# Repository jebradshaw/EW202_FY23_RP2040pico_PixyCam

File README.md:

# EW202_FY23_RP2040pico_PixyCam

  This PCB uses a Raspberry Pie RP2040 Pico microcontroller to interface with a PixyCam5 camera through an SPI interface to track a color object
using a dual servo pan and tilt platform.  There are also two potentiometers for a manual control of the servos.  This board is used in the WRC 
department at the US Naval Academy in support of the EW202 principles of Mechatronics course.

3D Rendering in KiCad of PCB

Schematic in KiCad

KiCad PCB file

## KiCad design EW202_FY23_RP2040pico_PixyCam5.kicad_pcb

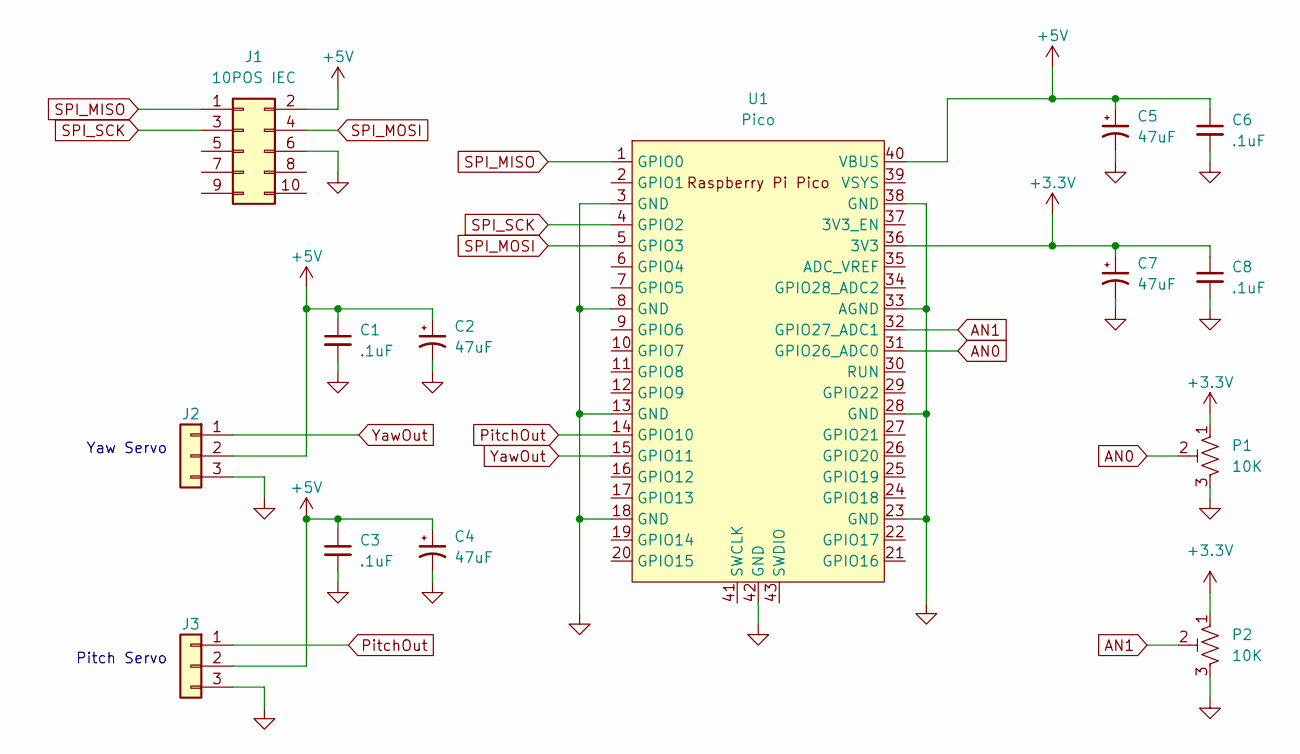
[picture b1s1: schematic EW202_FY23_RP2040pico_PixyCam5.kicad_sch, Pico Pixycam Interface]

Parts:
C1, C3, C6, C8: .1uF; C_Disc_D3.4mm_W2.1mm_P2.50mm
C2, C4, C5, C7: 47uF; CP_Radial_D5.0mm_P2.00mm
J1: 10POS IEC; IDC-Header_2x05_P2.54mm_Vertical
J2, J3: Conn_01x03; PinHeader_1x03_P2.54mm_Vertical
P1, P2: 10K; Potentiometer_Bourns_3362P-1-103TLF doublePads
U1: Pico; RPi_Pico_SMD_TH

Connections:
+3.3V: C7.1, C8.1, P1.1, P2.1, U1.36 (3V3)
+5V: C1.1, C2.1, C3.1, C4.1, C5.1, C6.1, J1.2, J2.2, J3.2, U1.40 (VBUS)
AN0: P1.2, U1.31 (GPIO26_ADC0)
AN1: P2.2, U1.32 (GPIO27_ADC1)
GND: C1.2, C2.2, C3.2, C4.2, C5.2, C6.2, C7.2, C8.2, J1.6, J2.3, J3.3, P1.3, P2.3, U1.3 (GND), U1.8 (GND), U1.13 (GND), U1.18 (GND), U1.23 (GND), U1.28 (GND), U1.33 (AGND), U1.38 (GND), U1.42 (GND)
PitchOut: J3.1, U1.14 (GPIO10)
SPI_MISO: J1.1, U1.1 (GPIO0)
SPI_MOSI: J1.4, U1.5 (GPIO3)
SPI_SCK: J1.3, U1.4 (GPIO2)
YawOut: J2.1, U1.15 (GPIO11)

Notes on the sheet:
Pitch Servo
Yaw Servo

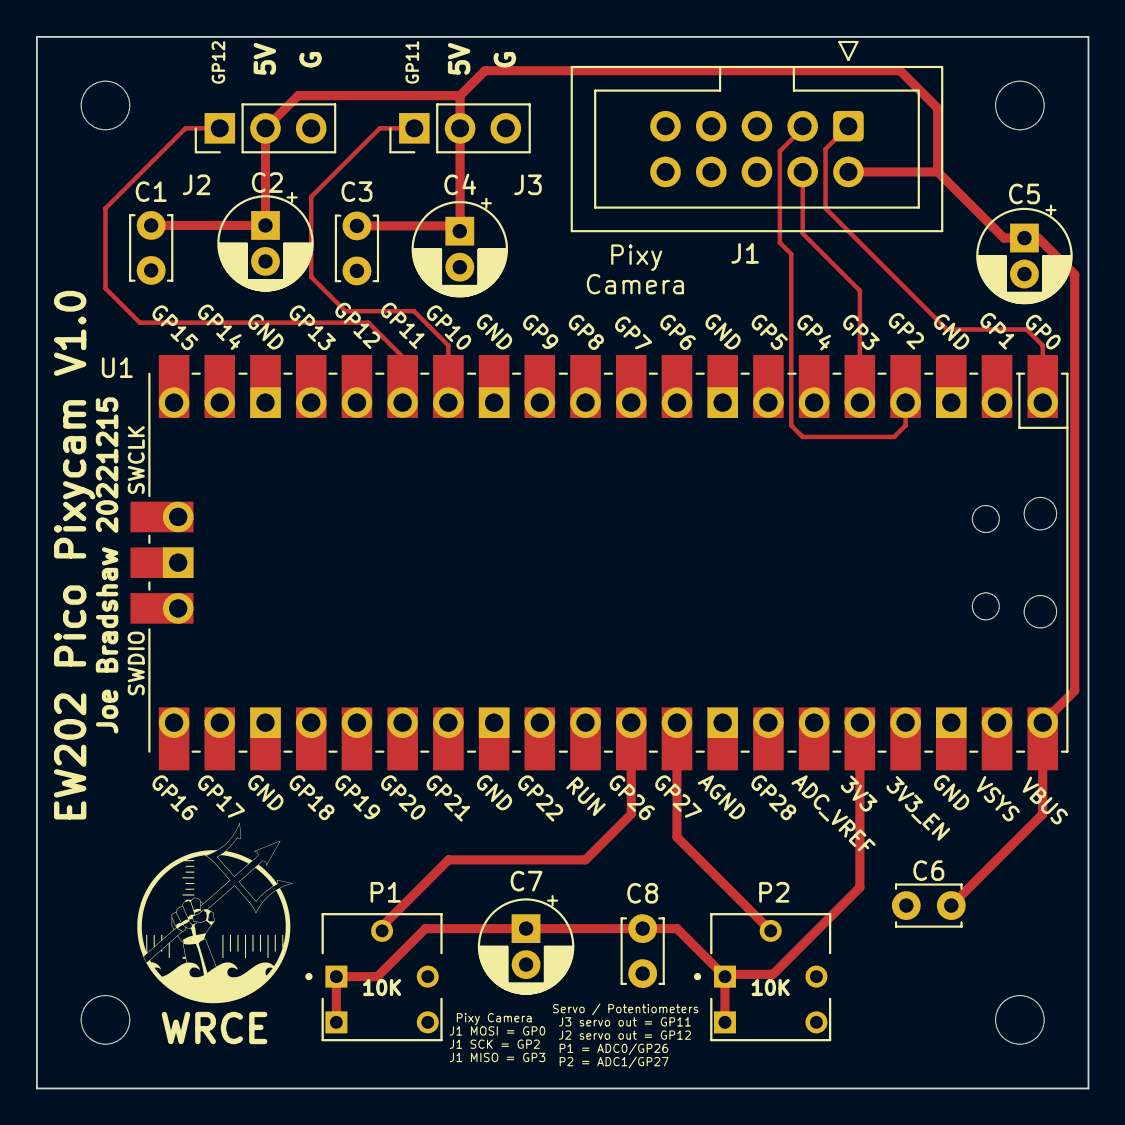
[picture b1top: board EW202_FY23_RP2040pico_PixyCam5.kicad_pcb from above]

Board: 2 copper layers, 58.4 x 58.4 mm, 18 parts (0 on the bottom side), 10 nets.

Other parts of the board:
M1, M2, M3, M4: MountingHole_2.7mm_M2.5
